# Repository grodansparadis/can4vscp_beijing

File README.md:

<h1>CAN4VSCP Beijing module</h1>

Beijing is a general I/O module that connects to a CAN4VSCP bus and can handle general I/O on ten channels that individually can be set as input or output. The module can be attached to a standard DIN Rail or be mounted directly on a wall (ordered as separate versions).

The module fully adopts to the CAN4VSCP specification and can be powered directly over the bus with a 9-28V DC power source. It has a rich register set for configuration and any information events defined. It also have a decision matrix for easy dynamic event handling.

VSCP CAN modules are designed to work on a VSCP4CAN bus which use ordinary RJ-45 connectors and is powered with 9-28V DC over the same cable. This means there is no need for a separate power cable. All that is needed is a CAT5 or better twisted pair cable. Buss length can be a maximum of 500 meters with drops of maximum 24 meters length (up to a total of 120 meters). As for all VSCP4CAN modules the communication speed is fixed at 125 kbps.

All VSCP modules contains information of there own setup, manual, hardware version, manufacturer etc. You just ask the module for the information you need and you will get it.

When they are started up they have a default functionality that often is all that is needed to get a working setup. If the module have something to report it will send you an event and if it is setup to react on a certain type of event it will do it's work when you send event(s) to it. 

<hr>

This project is part of the <a href="http://www.vscp.org">VSCP (Very Simple Control Protocol) project</a>. 

<hr>

## Project files

### User manual
  * [User Manual](https://grodansparadis.github.io/can4vscp_beijing/#)

### Schematic, PCB, 3D files etc
  * [Schematics reversion B](./eagle/beijing_sch_rev_B.png)
 * Hardware design files is made in [KiCad](https://kicad.org) and can be found in the `kicad` directory. Valid from reversion B of the hardware.
   * Gerber files for PCB production can be found in the `gerber` directory (in the `kicad` folder).
 * Eagle schema and board files for reversion A and B can be found in the `eagle` directory. They are no longer actively updated.

 ### Firmware

 The firmware is developed in [MPLAB X IDE](https://www.microchip.com/mplab/mplab-x-ide) using the [XC8 compiler](https://www.microchip.com/mplab/compilers).

  * Binary release files is available [here](https://github.com/grodansparadis/can4vscp_beijing/releases)

### MDF - Module Description File(s)
  * [MDF file version: 9 Release date: 2020-05-14](http://www.eurosource.se/beijing_2.xml)
  * [MDF file version: 1.0.0 Release date: 2015-06-15](http://www.eurosource.se/beijing_1.xml)

### Support
If you need support, please open an issue in the [GitHub repository](https://github.com/grodansparadis/can4vscp_kelvin_ntc10k/issues).

### Buy a ready made modules
You can buy a ready made module from [Grodans Paradis](http://www.grodansparadis.com).

### Project related links
  * [VSCP project](https://www.vscp.org)
  * [VSCP Documentation site](https://docs.vscp.org/)
  * [VSCP Wiki](https://github.com/grodansparadis/vscp/wiki)

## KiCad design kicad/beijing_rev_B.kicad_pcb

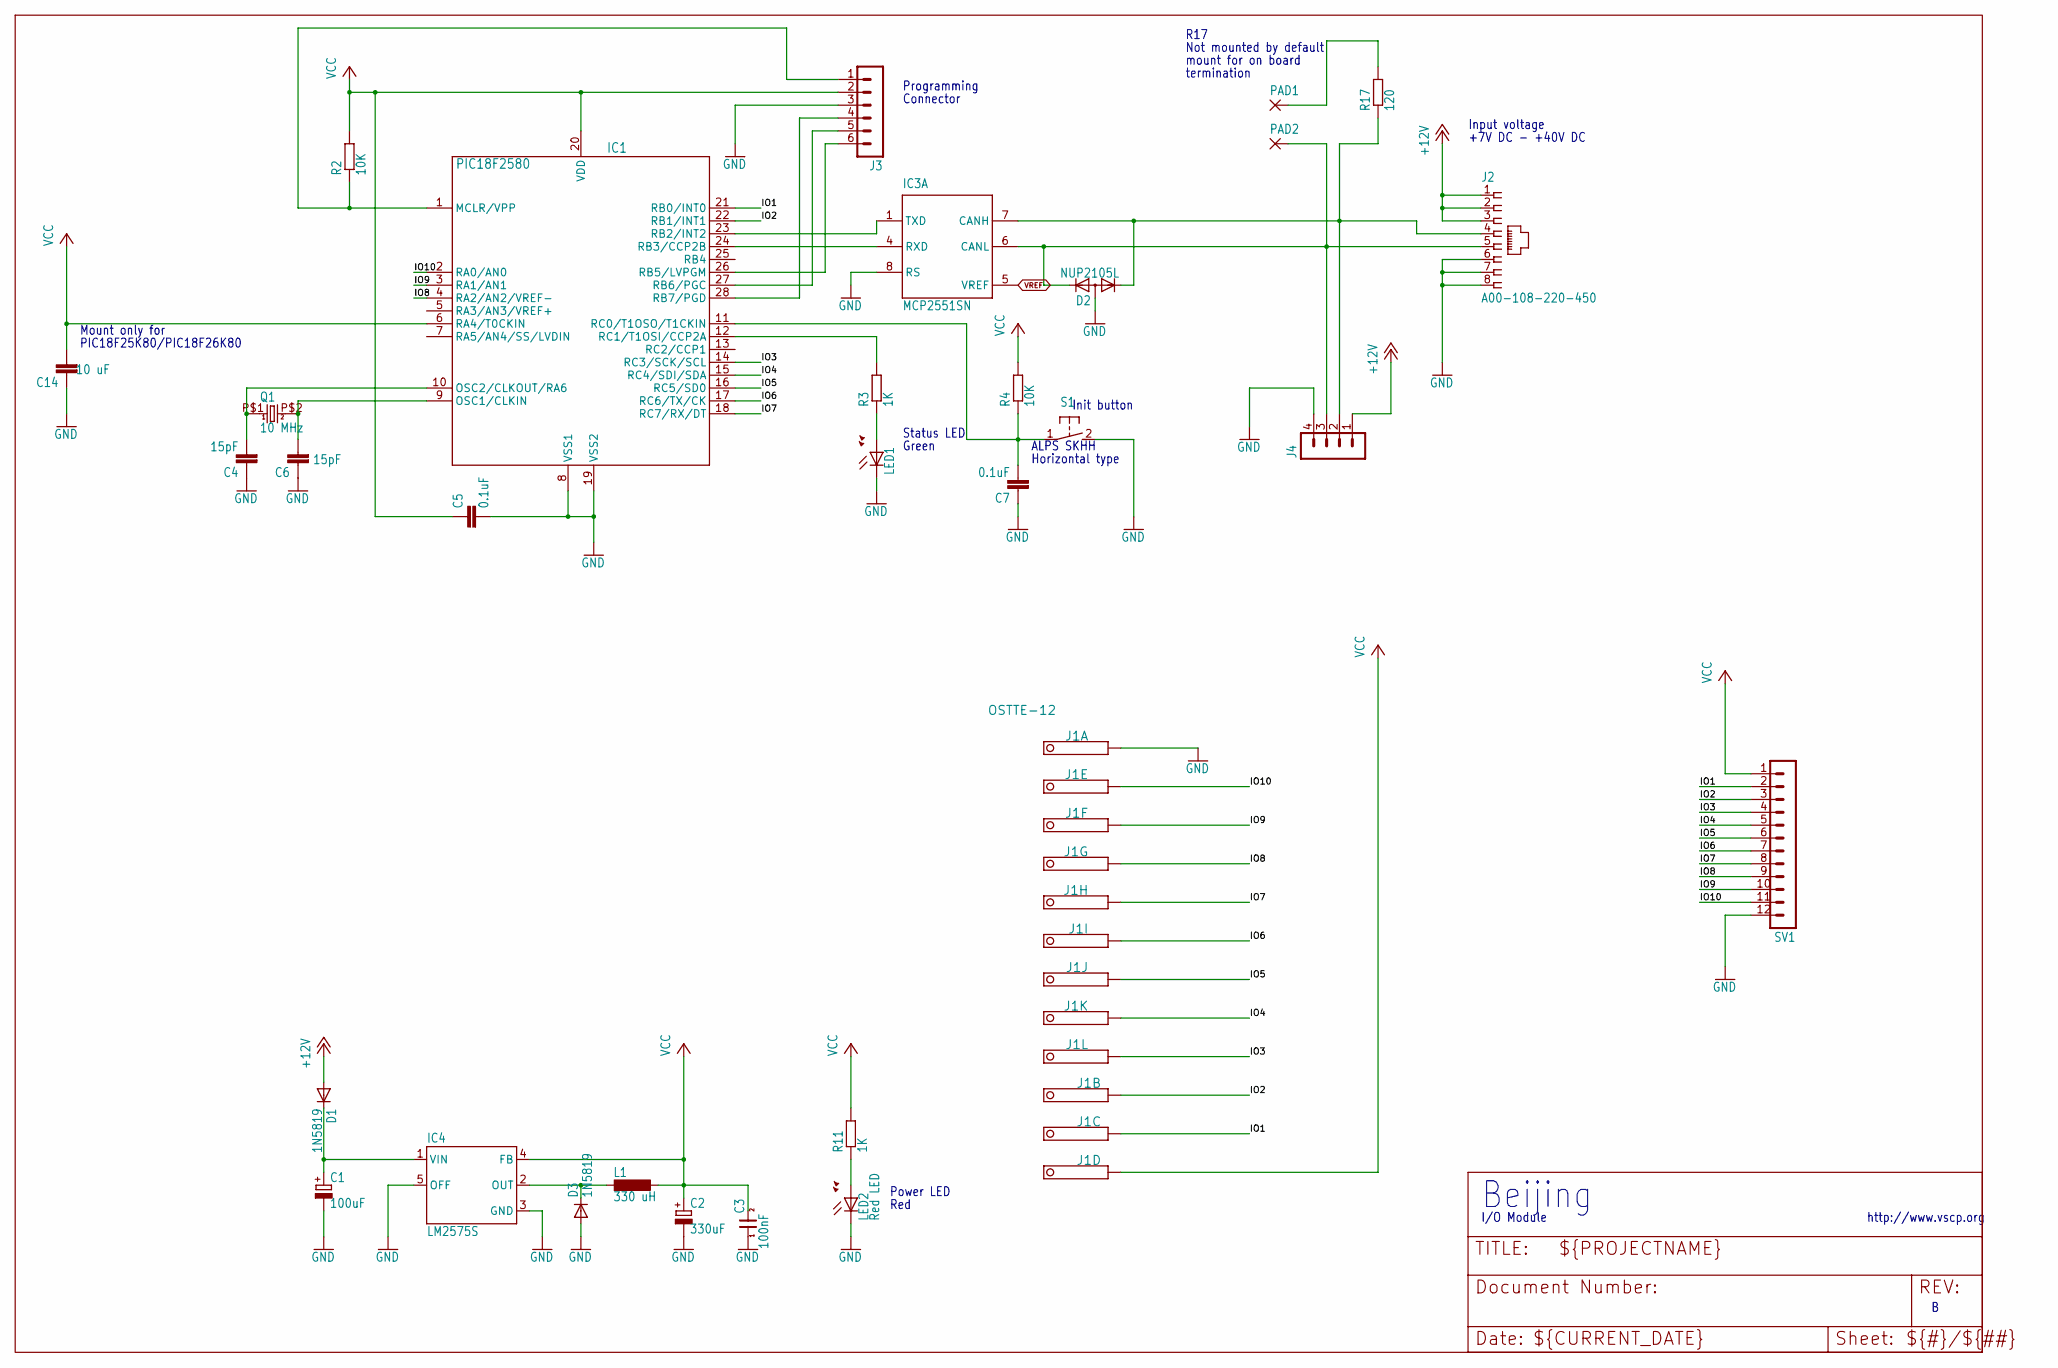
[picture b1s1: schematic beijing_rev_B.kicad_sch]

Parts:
C1: 100uF; PANASONIC_D
C2: 330uF; PANASONIC_D
C3: 100nF; 0805
C4, C6: 15pF; C0805
C5, C7: 0.1uF; C0805
C14: 10 uF; C0805
D1, D3: 1N5819; SOD123
D2: NUP2105L; SOT23
IC1: PIC18F2580; SO28
IC3: MCP2551SN; SO-08
IC4: LM2575S; TO263-5
J1: OSTTE-12; PINHEAD-12
J2: A00-108-220-450; RJ-45
J3: MA06-1
J4: MA04-1
L1: 330 uH; DO3316P
LED1: LEDCHIP-LED0805; CHIP-LED0805
LED2: Red LED; CHIP-LED0805
PAD1, PAD2: 1,6/0,8; 1,6_0,8
Q1: 10 MHz; 9C
R2, R4: 10K; R0805
R3, R11: 1K; R0805
R17: 120; R0805
S1: 31-XX; B3F-31XX
SV1: MA12-1

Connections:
+12V: D1.A, J2.1, J2.2, J2.3, J4.1
CANL: D2.2 (K2), IC3.6 (CANL), J2.5, J4.3, PAD2.1
GND: C1.-, C2.-, C3.1, C4.1, C5.2, C6.1, C7.1, C14.1, D2.3 (A), D3.A, IC1.8 (VSS1), IC1.19 (VSS2), IC3.2 (VSS), IC3.8 (RS), IC4.3 (GND), IC4.5 (OFF), J1.1, J2.6, J2.7, J2.8, J3.3, J4.4, LED1.C, LED2.C, S1.2 (S), SV1.12
IO1: IC1.21 (RB0/INT0), J1.11, SV1.2
IO2: IC1.22 (RB1/INT1), J1.10, SV1.3
IO3: IC1.14 (RC3/SCK/SCL), J1.9, SV1.4
IO4: IC1.15 (RC4/SDI/SDA), J1.8, SV1.5
IO5: IC1.16 (RC5/SD0), J1.7, SV1.6
IO6: IC1.17 (RC6/TX/CK), J1.6, SV1.7
IO7: IC1.18 (RC7/RX/DT), J1.5, SV1.8
IO8: IC1.4 (RA2/AN2/VREF-), J1.4, SV1.9
IO9: IC1.3 (RA1/AN1), J1.3, SV1.10
IO10: IC1.2 (RA0/AN0), J1.2, SV1.11
unnamed: D3.C, IC4.2 (OUT), L1.1
unnamed: C4.2, IC1.10 (OSC2/CLKOUT/RA6), Q1.P$1 (1)
unnamed: C1.+, D1.C, IC4.1 (VIN)
unnamed: IC1.12 (RC1/T1OSI/CCP2A), R3.2
unnamed: LED1.A, R3.1
unnamed: C7.2, IC1.11 (RC0/T1OSO/T1CKIN), R4.1, S1.1
unnamed: C6.2, IC1.9 (OSC1/CLKIN), Q1.P$2 (2)
unnamed: PAD1.1, R17.2
unnamed: IC1.1 (MCLR/VPP), J3.1, R2.1
unnamed: IC1.28 (RB7/PGD), J3.4
unnamed: IC1.27 (RB6/PGC), J3.5
unnamed: IC1.26 (RB5/LVPGM), J3.6
unnamed: LED2.A, R11.1
unnamed: D2.1 (K1), IC3.7 (CANH), J2.4, J4.2, R17.1
RXCAN: IC1.24 (RB3/CCP2B), IC3.4 (RXD)
TXCAN: IC1.23 (RB2/INT2), IC3.1 (TXD)
VCC: C2.+, C3.2, C5.1, C14.2, IC1.6 (RA4/T0CKIN), IC1.20 (VDD), IC3.3 (VDD), IC4.4 (FB), J1.12, J3.2, L1.2, R2.2, R4.2, R11.2, SV1.1
VREF: IC3.5 (VREF)

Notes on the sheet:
Status LED
Mount only for
Init button
R17
ALPS SKHH
Red
http://www.vscp.org
mount for on board
I/O Module
Not mounted by default
Connector
PIC18F25K80/PIC18F26K80
Input voltage
termination
Power LED
Beijing
Green
Horizontal type
+7V DC - +40V DC
Programming

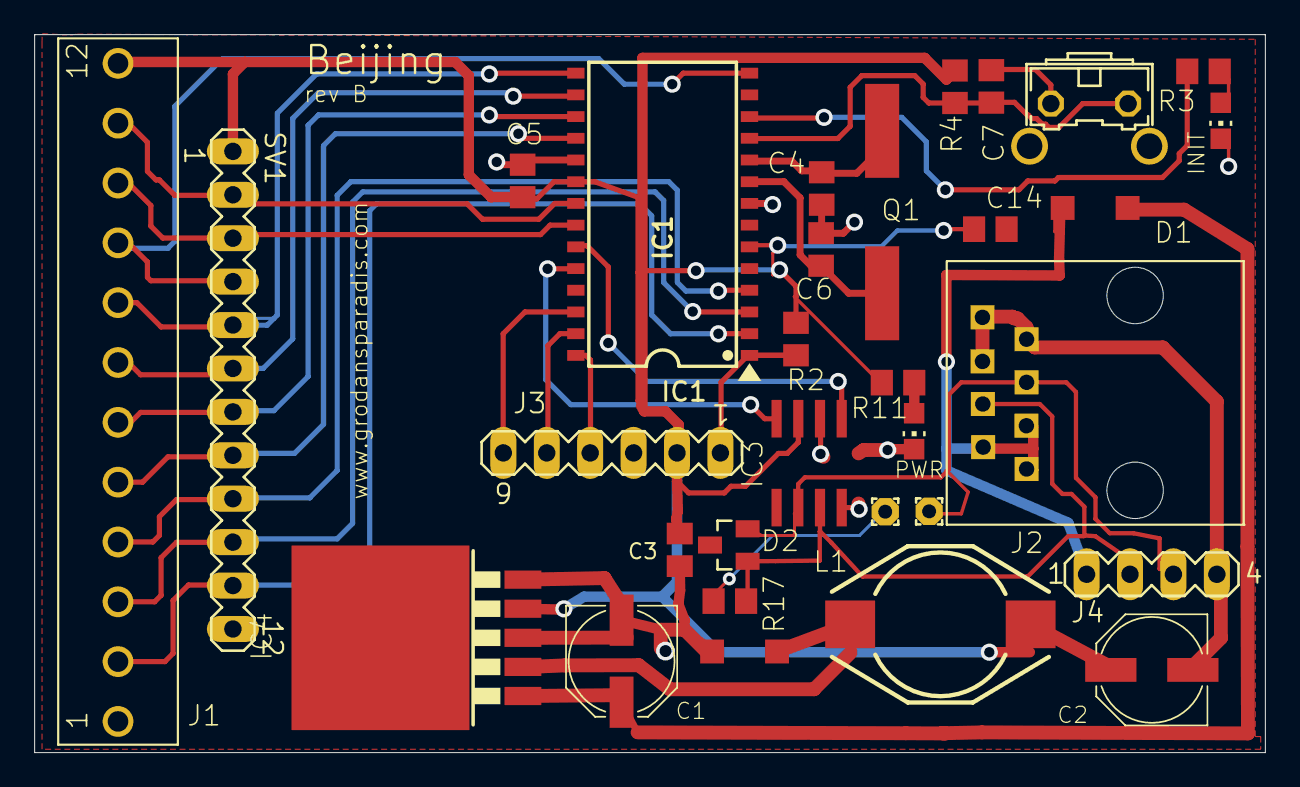
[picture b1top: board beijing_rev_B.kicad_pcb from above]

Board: 6 copper layers, 72.0 x 42.0 mm, 31 parts (0 on the bottom side), 30 nets.

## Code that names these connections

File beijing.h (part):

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//
#define TIMER2_RELOAD_VALUE                 156

#define STATUS_LED                          PORTCbits.RC1
#define INIT_BUTTON                         PORTCbits.RC0

// Defines for channels LATBbits.LATB0
#define CHANNEL0                            PORTBbits.RB0
#define CHANNEL1                            PORTBbits.RB1
#define CHANNEL2                            PORTCbits.RC3
#define CHANNEL3                            PORTCbits.RC4
#define CHANNEL4                            PORTCbits.RC5
#define CHANNEL5                            PORTCbits.RC6
#define CHANNEL6                            PORTCbits.RC7
#define CHANNEL7                            PORTAbits.RA2
#define CHANNEL8                            PORTAbits.RA1
#define CHANNEL9                            PORTAbits.RA0

#define LATCH_CHANNEL0                      LATBbits.LATB0
#define LATCH_CHANNEL1                      LATBbits.LATB1
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
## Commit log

2015-06-15 Initial checkin
2015-06-15 Cleaing up some junk
2015-06-15 Updated DM
2015-06-15 Edited
2015-06-15 Moved old design out of the way.
2015-06-18 All constants fixed
2015-06-18 Working with read regs
2015-06-24 Changed eeprom read/writes to peripheral ones
2015-06-25 Pulse working
2015-06-26 All registers read/written correctly
2015-07-02 Working with DM
2015-07-03 DM working
2015-07-05 Ready for release
2015-07-11 Added hex files
2015-07-27 Fixed problem with send timeout
2015-08-17 Changed license to Artistic License 3.0
2015-11-10 Fixed bug: start up initialization of I/O 7 was not initialized. Dynamic filter calculations was not done when DM was initialized.
2015-11-10 Added readme file for firmware folder.
2015-11-13 Added firmware readme
2015-11-15 Preparing for version 1.1.0.
2015-11-17 Request for decision matrix information returned invalid information. Fixed
2015-11-27 Fixed bug that caused channel 8/9 channels not to work in button input mode
2015-12-17 Updated license and readme
2015-12-17 Changed copyright info in headers so it is correct
2015-12-22 Added connector images
2016-02-04 Update HISTORY.txt
    Fixed spelling error
2016-03-04 Test registersets
2016-03-08 Sync between systems
2016-03-08 2016-03-08 AKHE - Adopted to 1.6 firmware. Adopted for PIC18F26K80.
2016-03-08 Updated copyright info.
2016-03-09 Just behind
2016-03-22 Firmware with new VSCP framworkd code
2016-03-22 Testing init. bug
2016-03-23 Changed environment
2016-03-23 Version 1.1.5
2016-04-04 Changed value of C14 to 10uF
2016-04-11 vscp_getMatrixInfo nw use the pointer supplied by the framework.
2016-04-19 RA4 set to input to prevent collision with VCAP circuits in PIC18F2580. Brown out raised to maximum (3V & 4.6V). Valuable input from Anders Forsgren, AJE Electronics AB.
2016-05-04 Changed bit time calculation link
2016-05-12 Wrong mask used. Thanks Steve
2016-05-17 Acrion on for channel 9 wrong, fixed. Credits Steve Skula
2016-05-17 Fixed typo in doActionOff, do ActionPulseOn and do ActionPulseOff Credets Steve S.
2016-05-24 Added pullup picture
2016-10-13 Added a new action shortpulse and a new register (0:47) for the timing. The shortpulse functionality is intended for bistable relays.
2016-10-18 Fixes #5
2016-10-18 MDF for short pulse had wrong action code (6), should be 8.
2016-10-19 Added some stock images
2016-10-19 Pulse output in place. Changed to 1 ms resolution instead of 10 ms.
2016-10-20 Added missing on-event flaggings as ntified by Steve Skula
2016-10-21 Added event logic to pulse output addition
2016-10-21 Added subzone specific check to short pulse
2016-10-24 Fixed init. problem for protection timer reported by Steve Skula
2016-10-24 on/off events now only when enabled also for short pulse
2020-05-14 init button now at 2500 ms, seconds counter fixed. VSCP core 1.6.3
2020-05-15 Updated copyright dates
2020-10-28 kicad conversion of schema and board
2020-11-04 Renamed missnamed files
2022-04-06 Updated picture content in MDF
2022-04-06 mdf: Added target code to firmware
2022-04-06 Removed patreon funding option
2025-08-18 Convert schema to kicad
2025-09-05 Initial manual
2025-09-05 Moved images to docs
2025-09-05 Correcyed schema rev B path
2025-09-05 Corrected schema rev B path again
2025-09-05 Added missing logo file
2025-09-05 Changed path for logo
2025-09-05 Changed log path
2025-09-05 Fixed index links
2025-09-05 Added logo files
2025-09-05 Smaller VSCP logo on cover page
2025-09-05 Added nojekyll

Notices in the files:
beijing.h:
Copyright (C) 1995-2005 Ake Hedman, eurosource
Copyright (C) 1995-2020 Ake Hedman, Grodans Paradis AB
This work is licensed under the Creative Common
http://creativecommons.org/licenses/by-nc-sa/3.0/legalcode
http://creativecommons.org/licenses/by-nc-sa/3.0
